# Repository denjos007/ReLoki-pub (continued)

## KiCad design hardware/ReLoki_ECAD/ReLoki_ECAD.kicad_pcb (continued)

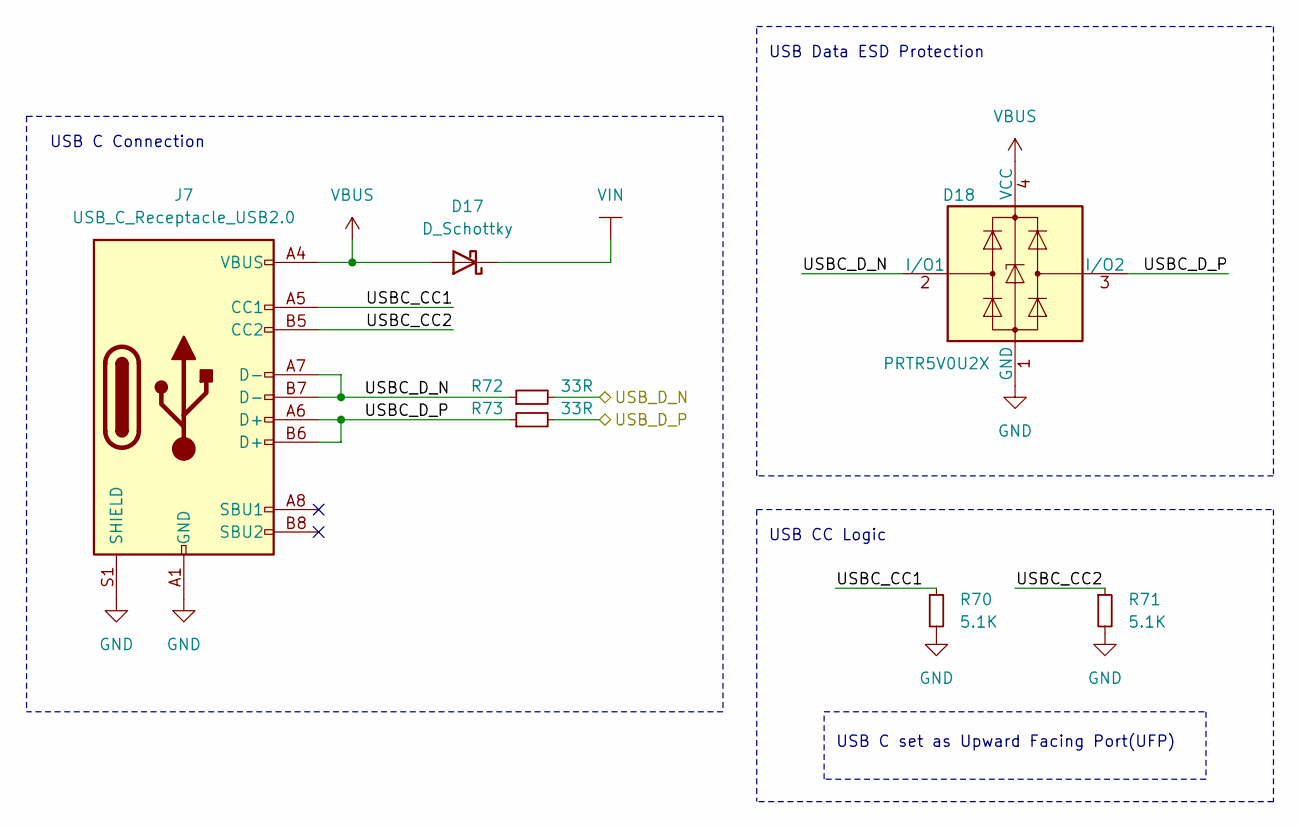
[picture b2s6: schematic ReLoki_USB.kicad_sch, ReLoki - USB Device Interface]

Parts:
D17: D_Schottky; D_SOD-123F
D18: PRTR5V0U2X; SOT-143
J7: USB_C_Receptacle_USB2.0; USB_C_Receptacle_XKB_U262-16XN-4BVC11
R70, R71: 5.1K; R_0402_1005Metric
R72, R73: 33R; R_0402_1005Metric

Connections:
/Microcontroller/USB1_D_N: R72.2; also elsewhere on the board
/Microcontroller/USB1_D_P: R73.2; also elsewhere on the board
/USB-C/USBC_CC1: J7.A5 (CC1), R70.1
/USB-C/USBC_CC2: J7.B5 (CC2), R71.1
/USB-C/USBC_D_N: D18.2 (I/O1), J7.A7 (D-), J7.B7 (D-), R72.1
/USB-C/USBC_D_P: D18.3 (I/O2), J7.A6 (D+), J7.B6 (D+), R73.1
GND: D18.1 (GND), J7.A1 (GND), J7.A12 (GND), J7.B1 (GND), J7.B12 (GND), J7.S1 (SHIELD), R70.2, R71.2; also elsewhere on the board
VBUS: D17.2 (A), D18.4 (VCC), J7.A4 (VBUS), J7.A9 (VBUS), J7.B4 (VBUS), J7.B9 (VBUS)
VIN: D17.1 (K); also elsewhere on the board

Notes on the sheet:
USB Data ESD Protection
USB C set as Upward Facing Port(UFP)
USB CC Logic
USB C Connection

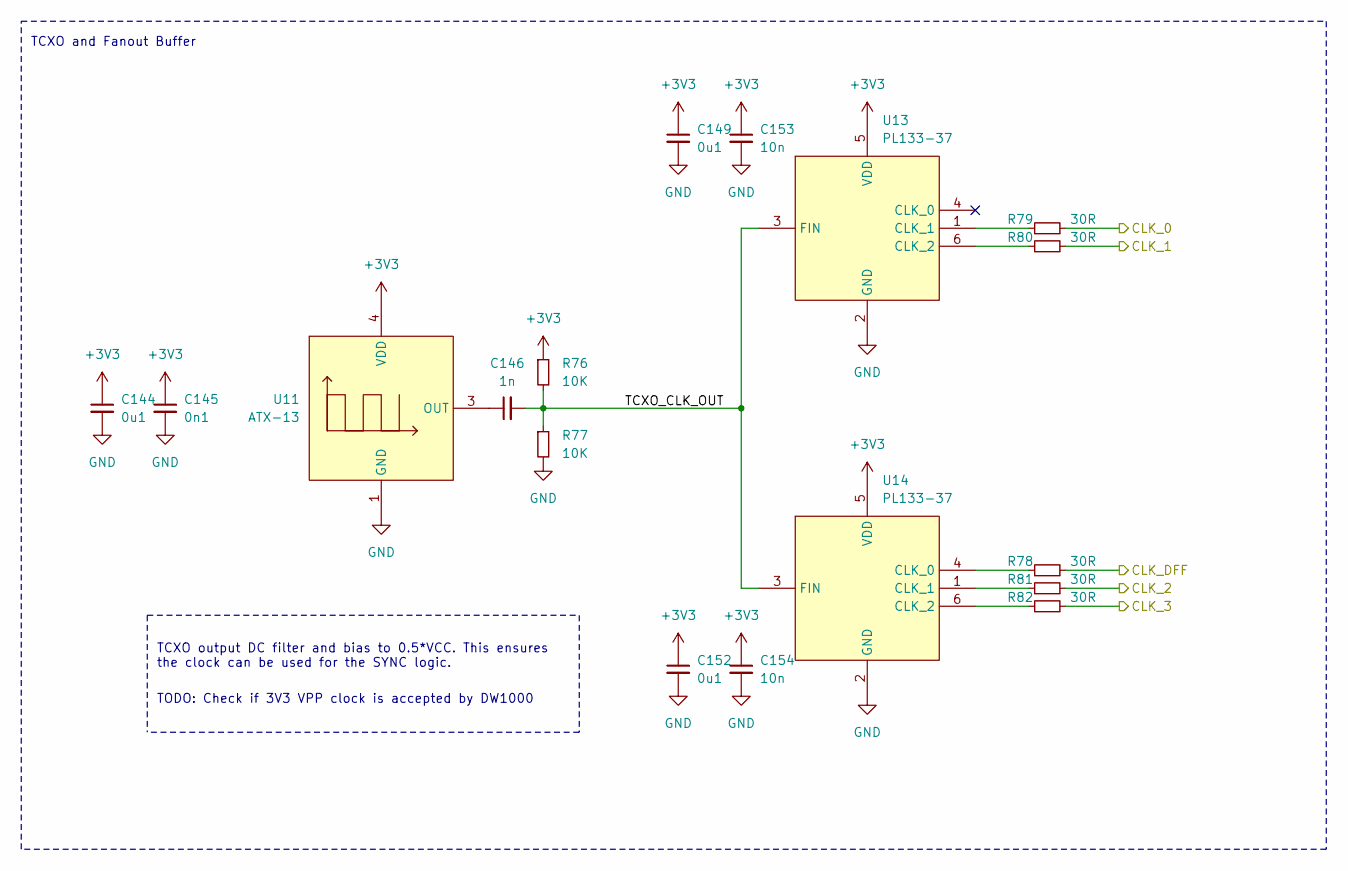
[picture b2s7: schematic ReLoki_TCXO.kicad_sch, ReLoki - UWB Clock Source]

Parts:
C144, C149, C152: 0u1; C_0402_1005Metric
C145: 0n1; C_0402_1005Metric
C146: 1n; C_0402_1005Metric
C153, C154: 10n; C_0402_1005Metric
R76, R77: 10K; R_0402_1005Metric
R78, R79, R80, R81, R82: 30R; R_0402_1005Metric
U11: ATX-13; Oscillator_SMD_Abracon_ATX13-4Pin_2.0x1.6mm
U13, U14: PL133-37; SOT-23-6

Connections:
+3V3: C144.1, C145.1, C149.1, C152.1, C153.1, C154.1, R76.1, U11.4 (VDD), U13.5 (VDD), U14.5 (VDD); also elsewhere on the board
/Microcontroller/CLK_DFF: R78.2; also elsewhere on the board
/TCXO/CLK_0: R79.2; also elsewhere on the board
/TCXO/CLK_1: R80.2; also elsewhere on the board
/TCXO/CLK_2: R81.2; also elsewhere on the board
/TCXO/CLK_3: R82.2; also elsewhere on the board
/TCXO/TCXO_CLK_OUT: C146.2, R76.2, R77.1, U13.3 (FIN), U14.3 (FIN)
GND: C144.2, C145.2, C149.2, C152.2, C153.2, C154.2, R77.2, U11.1 (GND), U11.2 (GND), U13.2 (GND), U14.2 (GND); also elsewhere on the board
unnamed: C146.1, U11.3 (OUT)
unnamed: R78.1, U14.4 (CLK_0)
unnamed: R79.1, U13.1 (CLK_1)
unnamed: R80.1, U13.6 (CLK_2)
unnamed: R81.1, U14.1 (CLK_1)
unnamed: R82.1, U14.6 (CLK_2)

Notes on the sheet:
TCXO output DC filter and bias to 0.5*VCC. This ensures the clock can be used for the SYNC logic.
TCXO and Fanout Buffer
TODO: Check if 3V3 VPP clock is accepted by DW1000

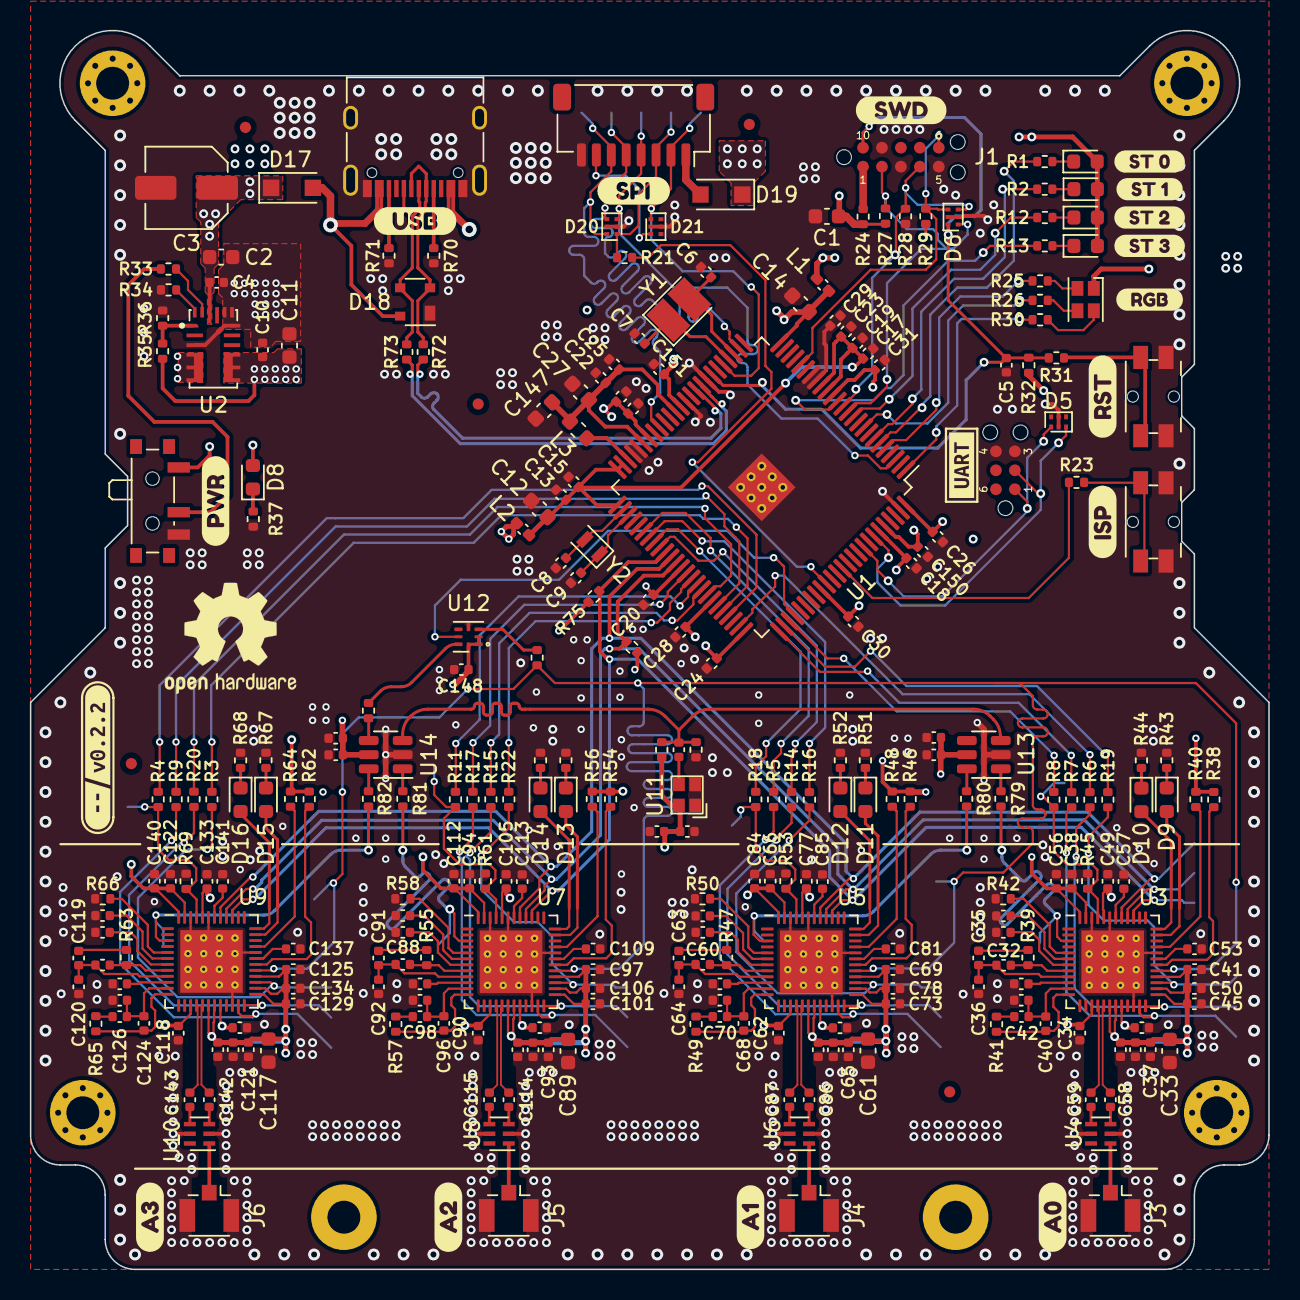
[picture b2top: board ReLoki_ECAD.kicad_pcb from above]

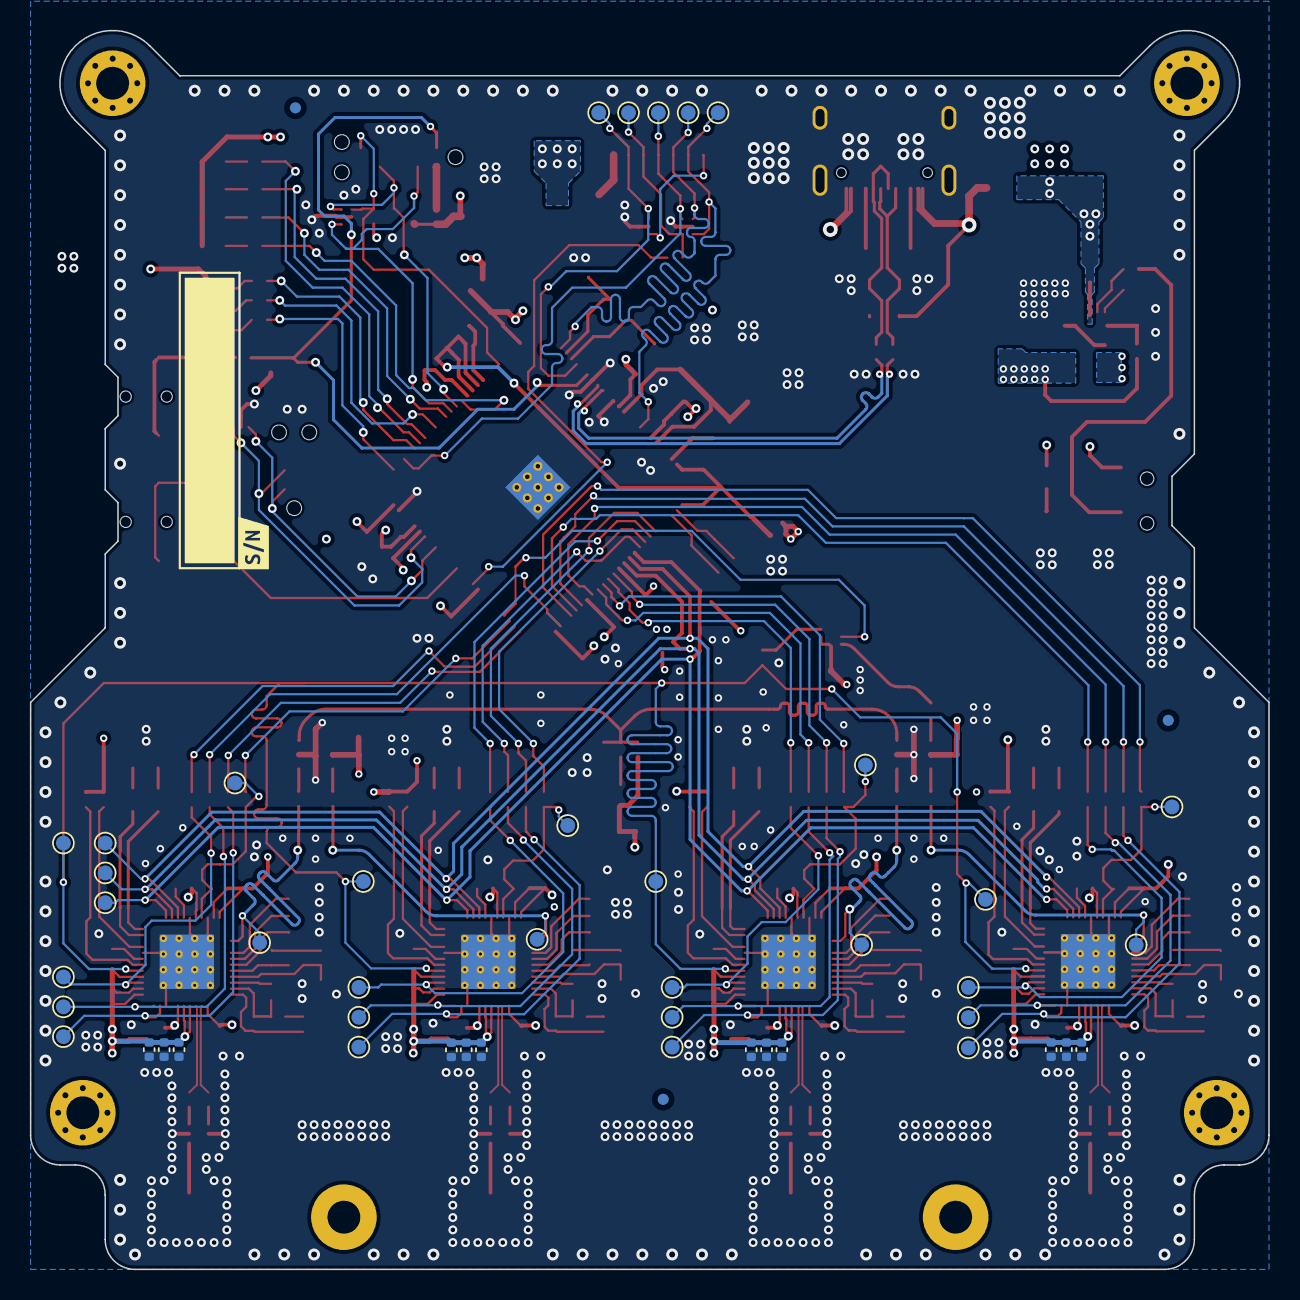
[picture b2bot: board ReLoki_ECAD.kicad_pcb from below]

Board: 4 copper layers, 83.0 x 83.0 mm, 352 parts (48 on the bottom side), 202 nets.

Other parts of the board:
kibuzzard-6352BF52: G***; kibuzzard-6352BF52
kibuzzard-6352BF92: G***; kibuzzard-6352BF92
kibuzzard-6352C04F: G***; kibuzzard-6352C04F
kibuzzard-6352C008: G***; kibuzzard-6352C008
kibuzzard-6352C032: G***; kibuzzard-6352C032
kibuzzard-6352C089: G***; kibuzzard-6352C089
kibuzzard-6352CA9B: G***; kibuzzard-6352CA9B
kibuzzard-6352CA75: G***; kibuzzard-6352CA75
kibuzzard-6352CA94: G***; kibuzzard-6352CA94
kibuzzard-6352CAA2: G***; kibuzzard-6352CAA2
kibuzzard-6352EB6B: G***; kibuzzard-6352EB6B
kibuzzard-6352EB8E: G***; kibuzzard-6352EB8E
kibuzzard-6352EB70: G***; kibuzzard-6352EB70
kibuzzard-6352EB77: G***; kibuzzard-6352EB77
kibuzzard-6352EB82: G***; kibuzzard-6352EB82
kibuzzard-66328E0B: G***; kibuzzard-66328E0B
kibuzzard-66328EE8: G***; kibuzzard-66328EE8
kibuzzard-66328F53: G***; kibuzzard-66328F53
kibuzzard-66328FDF: G***; kibuzzard-66328FDF

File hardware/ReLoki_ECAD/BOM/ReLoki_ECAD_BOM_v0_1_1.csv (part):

"Source:","/Users/joseph/Library/CloudStorage/OneDrive-GeorgeMasonUniversity-O365Production/Classwork/Research/Project_BlimpSquad/Projects/Multiagent_RelativeLocalization/hardware/ReLoki_ECAD/ReLoki_ECAD.kicad_sch"
"Date:","Thursday, October 27, 2022 at 10:31:55 AM"
"Tool:","Eeschema (6.0.8-1)-1"
"Generator:","/Applications/KiCad/KiCad.app/Contents/SharedSupport/plugins/bom_csv_grouped_by_value_with_fp.py"
"Component Count:","319"
"Ref","Qnty","Value","Cmp name","Footprint","Description","Vendor"
"C1, ","1","10u","C_Small","Capacitor_SMD:C_0603_1608Metric","Unpolarized capacitor, small symbol",""
"C2, ","1","4u7 35V","C_Small","Capacitor_SMD:C_0603_1608Metric","Unpolarized capacitor, small symbol",""
"C3, ","1","100uF 35V","C_Polarized_Small","Capacitor_SMD:C_Elec_5x5.8","Polarized capacitor, small symbol",""
"C4, ","1","10n 35V","C_Small","Capacitor_SMD:C_0402_1005Metric","Unpolarized capacitor, small symbol",""
"C5, C10, C18, C21, C23, C28, C29, C31, C34, C62, C90, C118, C150, C151, ","14","10n","C_Small","Capacitor_SMD:C_0402_1005Metric","Unpolarized capacitor, small symbol",""
"C6, C7, ","2","8p","C_Small","Capacitor_SMD:C_0402_1005Metric","Unpolarized capacitor, small symbol",""
"C8, C9, ","2","22p","C_Small","Capacitor_SMD:C_0402_1005Metric","Unpolarized capacitor, small symbol",""
"C11, C12, C147, ","3","22u","C_Small","Capacitor_SMD:C_0603_1608Metric","Unpolarized capacitor, small symbol",""
"C13, C16, C19, C20, C24, C25, C26, C30, C36, C37, C38, C41, C44, C45, C46, C47, C48, C49, C50, C51, C53, C54, C56, C57, C64, C65, C66, C69, C72, C73, C74, C75, C76, C77, C78, C79, C81, C82, C84, C85, C92, C93, C94, C97, C100, C101, C102, C103, C104, C105, C106, C107, C109, C110, C112, C113, C120, C121, C122, C125, C128, C129, C130, C131, C132, C133, C134, C135, C137, C138, C140, C141, ","72","0u1","C_Small","Capacitor_SMD:C_0402_1005Metric","Unpolarized capacitor, small symbol",""
"C14, ","1","4u7","C_Small","Capacitor_SMD:C_0603_1608Metric","Unpolarized capacitor, small symbol",""
"C15, C17, C22, ","3","47p","C_Small","Capacitor_SMD:C_0402_1005Metric","Unpolarized capacitor, small symbol",""
"C27, ","1","2u2","C_Small","Capacitor_SMD:C_0603_1608Metric","Unpolarized capacitor, small symbol",""
"C32, C60, C88, C116, ","4","1p2","C_Small","Capacitor_SMD:C_0402_1005Metric","Unpolarized capacitor, small symbol",""
"C33, C61, C89, C117, ","4","47u","C_Small","Capacitor_SMD:C_0603_1608Metric","Unpolarized capacitor, small symbol",""
"C35, C63, C91, C119, ","4","27p","C_Small","Capacitor_SMD:C_0402_1005Metric","Unpolarized capacitor, small symbol",""
"C39, C52, C67, C80, C95, C108, C123, C136, ","8","10p","C_Small","Capacitor_SMD:C_0402_1005Metric","Unpolarized capacitor, small symbol",""
"C40, C68, C96, C124, ","4","18p","C_Small","Capacitor_SMD:C_0402_1005Metric","Unpolarized capacitor, small symbol",""
"C42, C70, C98, C126, ","4","820p","C_Small","Capacitor_SMD:C_0402_1005Metric","Unpolarized capacitor, small symbol",""
"C43, C55, C71, C83, C99, C111, C127, C139, ","8","330p","C_Small","Capacitor_SMD:C_0402_1005Metric","Unpolarized capacitor, small symbol",""
"C58, C59, C86, C87, C114, C115, C142, C143, ","8","12p","C_Small","Capacitor_SMD:C_0402_1005Metric","Unpolarized capacitor, small symbol",""
"C144, C148, ","2","4u7","C_Small","Capacitor_SMD:C_0402_1005Metric","Unpolarized capacitor, small symbol",""
"C145, C149, ","2","0n1","C_Small","Capacitor_SMD:C_0402_1005Metric","Unpolarized capacitor, small symbol",""
"C146, ","1","1n","C_Small","Capacitor_SMD:C_0402_1005Metric","Unpolarized capacitor, small symbol",""
"D1, D2, D3, D4, D9, D11, D13, D15, ","8","LED_G","LED_Small","LED_SMD:LED_0603_1608Metric","Light emitting diode, small symbol",""
"D5, D6, D20, D21, ","4","PESD3V3L4UF","PESD3V3L4UF","Package_TO_SOT_SMD:SOT-886","Low capacitance unidirectional quadruple ESD protection diode array, 3.3V, Common Anode, SOT-886",""
"D7, ","1","LED_ABGR","LED_ABGR","LED_SMD:LED_Cree-PLCC4_2x2mm_CW","RGB LED, anode/blue/green/red",""
"D8, ","1","LED_R","LED_Small","LED_SMD:LED_0603_1608Metric","Light emitting diode, small symbol",""
"D10, D12, D14, D16, ","4","LED_B","LED_Small","LED_SMD:LED_0603_1608Metric","Light emitting diode, small symbol",""
"D17, D19, ","2","D_Schottky","D_Schottky","Diode_SMD:D_SOD-123F","Schottky diode",""
"D18, ","1","PRTR5V0U2X","PRTR5V0U2X","Package_TO_SOT_SMD:SOT-143","Ultra low capacitance double rail-to-rail ESD protection diode, SOT-143",""
"FID1, FID2, FID3, FID4, FID5, FID6, FID7, FID8, ","8","Fiducial","Fiducial","Fiducial:Fiducial_0.75mm_Mask1.5mm","Fiducial Marker",""
"H1, H2, H3, H4, ","4","MountingHole","MountingHole","MountingHole:MountingHole_2.2mm_M2_Pad_Via","Mounting Hole without connection",""
"H5, H6, ","2","MountingHole","MountingHole","MountingHole:MountingHole_2.2mm_M2_Pad","Mounting Hole without connection",""
"J1, ","1","TC2050","Conn_02x05_Counter_Clockwise","Tag-Connect:TC2050-IDC-NL","Generic connector, double row, 02x05, counter clockwise pin numbering scheme (similar to DIP package numbering), script generated (kicad-library-utils/schlib/autogen/connector/)",""
"J2, ","1","TC2030","Conn_02x03_Counter_Clockwise","Tag-Connect:TC2030-IDC-NL","Generic connector, double row, 02x03, counter clockwise pin numbering scheme (similar to DIP package numbering), script generated (kicad-library-utils/schlib/autogen/connector/)",""
"J3, J4, J5, J6, ","4","Uf.l","Conn_Coaxial","Connector_Coaxial:U.FL_Hirose_U.FL-R-SMT-1_Vertical","coaxial connector (BNC, SMA, SMB, SMC, Cinch/RCA, LEMO, ...)",""
"J7, ","1","USB_C_Receptacle_USB2.0","USB_C_Receptacle_USB2.0","Connector_USB:USB_C_Receptacle_XKB_U262-16XN-4BVC11","USB 2.0-only Type-C Receptacle connector",""
"J8, ","1","JST_SH_SM08B","Conn_01x08","Connector_JST:JST_SH_SM08B-SRSS-TB_1x08-1MP_P1.00mm_Horizontal","Generic connector, single row, 01x08, script generated (kicad-library-utils/schlib/autogen/connector/)",""
"L1, L2, ","2","Ferrite","L_Small","Inductor_SMD:L_0402_1005Metric_Pad0.77x0.64mm_HandSolder","Inductor, small symbol",""
"L3, ","1","4.7u","L_Small","Inductor_SMD:L_0603_1608Metric","Inductor, small symbol",""
"R1, R2, R12, R13, R25, ","5","280R","R_Small","Resistor_SMD:R_0402_1005Metric","Resistor, small symbol",""
"R3, R4, R5, R6, R7, R8, R9, R10, R11, R14, R15, R16, R17, R18, R19, R20, R21, R22, R24, ","19","0R","R_Small","Resistor_SMD:R_0402_1005Metric","Resistor, small symbol",""
"R23, ","1","2k2","R_Small","Resistor_SMD:R_0402_1005Metric","Resistor, small symbol",""
"R26, ","1","80R","R_Small","Resistor_SMD:R_0402_1005Metric","Resistor, small symbol",""
"R27, R28, R29, R38, R46, R54, R62, ","7","10K","R_Small","Resistor_SMD:R_0402_1005Metric","Resistor, small symbol",""
"R30, ","1","60R","R_Small","Resistor_SMD:R_0402_1005Metric","Resistor, small symbol",""
"R31, ","1","100R","R_Small","Resistor_SMD:R_0402_1005Metric","Resistor, small symbol",""
"R32, ","1","100K","R_Small","Resistor_SMD:R_0402_1005Metric","Resistor, small symbol",""
"R33, ","1","55K","R_Small","Resistor_SMD:R_0402_1005Metric","Resistor, small symbol",""
"R34, ","1","62K","R_Small","Resistor_SMD:R_0402_1005Metric","Resistor, small symbol",""
"R35, ","1","75K","R_Small","Resistor_SMD:R_0402_1005Metric","Resistor, small symbol",""
"R36, ","1","24K","R_Small","Resistor_SMD:R_0402_1005Metric","Resistor, small symbol",""
"R37, R41, R43, R44, R49, R51, R52, R57, R59, R60, R65, R67, R68, ","13","270R","R_Small","Resistor_SMD:R_0402_1005Metric","Resistor, small symbol",""
"R39, R47, R55, R63, ","4","16k","R_Small","Resistor_SMD:R_0402_1005Metric","Resistor, small symbol",""
"R40, R45, R48, R53, R56, R61, R64, R69, ","8","10K DNP","R_Small","Resistor_SMD:R_0402_1005Metric","Resistor, small symbol",""
"R42, R50, R58, R66, ","4","11K 1%","R_Small","Resistor_SMD:R_0402_1005Metric","Resistor, small symbol",""
"R70, R71, ","2","5.1K","R_Small","Resistor_SMD:R_0402_1005Metric","Resistor, small symbol",""
"R72, R73, ","2","33R","R_Small","Resistor_SMD:R_0402_1005Metric","Resistor, small symbol",""
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
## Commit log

2024-08-30 Add all hardware files from private repo to public.
2024-08-30 Add hardware description
